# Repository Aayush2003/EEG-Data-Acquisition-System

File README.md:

# EEG Data Acquisition System

This repository contains all the work we've done as part of the course project in EE344: Electronic Design Lab

Team Members:
* Aayush Rajesh
* Anubhav Bhatla
* Aditya Sriram
* Ankith R
* Nithish Kumar Reddy
* Shivam Patel

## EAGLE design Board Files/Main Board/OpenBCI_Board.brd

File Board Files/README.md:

## PCB Design Files  

* The Base ADC Board is a modular unit which houses a single ADS1194 ADC placed on a standard 64-pin breakout board. The unit can interface with 4-channel differential electrodes and a microcontroller. In case of use in a Daisy-chain, this must be the base ADC (```DAISY_IN``` grounded) as it provides the sampling clock to all other ADCs in the chain.  
* The Daisy ADC Board is a modular unit similar to the Base ADC Board, and is meant to be connected in a Daisy-chain. Breakout pins on the board facillitate the connection according to Daisy-chain specifications.  
* The Main Board is a single, large PCB which can house 6 ADS1194 ADCs (and hence has a channel count of 24). It also has provisions for a PIC32MX microcontroller, a Wi-Fi chip, an SD card holder, and an accelerometer.

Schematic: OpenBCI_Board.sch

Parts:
C1: 10n; CAPC1608X85
C2, C4: 2.2u; CAPC1608X85
C3, C13, C23, C33, C41, C49, C56, C64, C124: 10u; CAPC3216X135
C5, C6, C8, C9, C15, C16, C19, C20, C24, C27, C29, C31, C35, C36, C38, C43, C44, C46, C51, C52, C54, C59, C60, C62, C67, C68, C70, C129, C131, C135, C137, C139, C141, C143, C145, C160, C162, C164, C166, C168, C170, C174, C176, C178, C180, C182, C184, C188, C190, C192, C194, C196, C198, C202, C204, C206, C208, C210, C212, C216, C218, C220, C222, C224, C226, C230, C232, C234, C236, C238, C240, C244, C246, C248, C250, C252, C254, C258, C260, C262, C264, C266, C268, C272, C274, C276, C278, C280, C282, C286, C288, C290, C292, C294, C296, C300: 1u; CAPC2012X110
C7, C12, C17, C21, C22, C26, C28, C30, C32, C37, C40, C45, C48, C53, C57, C61, C65, C69, C128, C130, C134, C136, C138, C140, C142, C144, C146, C147, C150, C151, C159, C161, C163, C165, C167, C169, C173, C175, C177, C179, C181, C183, C187, C189, C191, C193, C195, C197, C201, C203, C205, C207, C209, C211, C215, C217, C219, C221, C223, C225, C229, C231, C233, C235, C237, C239, C243, C245, C247, C249, C251, C253, C257, C259, C261, C263, C265, C267, C271, C273, C275, C277, C279, C281, C285, C287, C289, C291, C293, C295, C299: 0.1u; CAPC2012X110
C10, C11: 3.3u; CAPC1608X85
C14, C34, C42, C50, C58, C66: 22u; CAPC3216X135
C18: 10u; CAP_MCVV_A1_MTC-L
C25, C39, C47, C55, C63, C71: 100p; CAPC1608X85
C72, C73, C74, C76, C77, C78, C79, C80, C81, C82, C83, C84, C85, C86, C87, C88, C89, C90, C91, C92, C93, C94, C95, C96, C97, C98, C99, C100, C101, C102, C103, C104, C105, C106, C107, C108, C109, C110, C111, C112, C113, C114, C115, C116, C117, C118, C119, C121, C122, C123, C152, C153, C154, C155, C156: 10p; CAPC1608X85
C125, C126: 15p; CAPC1608X85
C127: 1.5n; CAPC1608X85
CR1, CR2: BAT85; DO-34_NEX
D1, D3: LED_BLUE; LEDC3216X75N_FLAT-B
D2: LED_BLUE; LEDC1005X25N_FLAT-B
ESP-BOOT: 10-XX; B3F-10XX
ESP-RST: 10-XX; B3F-10XX
FB1, FB2, FB3, FB5, FB6, FB9: FERRITE_BEAD; BEADC1608X95N
J3: SDCARD; GCT_MEM2051-00-195-00-A_REVD1
JP1, JP2, JP3, JP20, JP21, JP22: PINHD-2X5/90; 2X05/90
JP4, JP11, JP23: PINHD-1X2; 1X02
JP5, JP6: PINHD-2X2/90; 2X02/90
JP7: PINHD-1X10; 1X10
JP8: PINHD-1X8; 1X08
JP9, JP19: PINHD-1X4; 1X04
JP10: PINHD-1X3; 1X03
JP12: PINHD-1X7; 1X07
JP13, JP14, JP15, JP16, JP18: PINHD-1X1; 1X01
JP17: AGND; 1X01
MCLR/RESET: 10-XX; B3F-10XX
PIC-BOOT: PIC-BOOT; B3F-10XX
R1, R2, R4, R6, R7, R8, R61: 10k; RESC1608X60
R3, R5, R63, R66: 1k; RESC1608X60
R10, R11, R12, R13, R14, R15, R16, R17, R18, R19, R20, R21, R22, R23, R24, R25, R26, R27, R28, R29, R30, R31, R32, R33, R34, R35, R36, R37, R38, R39, R40, R41, R42, R43, R44, R45, R46, R47, R48, R49, R50, R51, R52, R53, R54, R55, R56, R57, R58, R59, R68, R69, R70, R71, R72: 5k; RESC1608X60
R62, R65: 1M; RESC1608X60
R64: 470k; RESC1608X60
R67: 0; RESC1608X60
U1: ESP-07SESP-07S_RFS-L; ESP-07S_RFS-L
U2: TPS72325DBVTDBV0005A; DBV0005A
U3: TLV70012QDDCRQ1DDC5_TEX-L; DDC5_TEX-L
U4, U6: AP2112K-3.3TRG1SOT_RG1_DIO-L; SOT_RG1_DIO-L
U5: LM2664M6; SOT95P280X145-6N
U7: LIS3DHHTRQFN; QFN_ICLX_STM
U8, U9, U10, U11, U12, U13: ADS1194CPAGPAG64-L; PAG64-L
U14, U15, U16, U17, U18, U19, U20, U21, U22, U23, U24, U25, U26, U27, U30: TPD4E1B; DCK6_TEX-L
U28: PIC32MX250F128D-50I/PTTQFP44_MC_MCH-L; TQFP44_MC_MCH-L
XTAL1: 8M; XTALRR488W45L1150T500H350B

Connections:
1N: JP20.7, R57.1, U25.4 (IO3)
1P: JP20.8, R58.1, U26.1 (IO1)
2N: JP20.5, R55.1, U25.2 (IO2)
2P: JP20.6, R56.1, U25.5 (IO4)
3N: JP20.3, R53.1, U24.4 (IO3)
3P: JP20.4, R54.1, U25.1 (IO1)
3V3: C19.1, C22.1, C23.1, D2.A, JP9.1, R1.2, R2.2, R4.2, U1.8 (VCC), U4.5 (VOUT)
4N: JP20.1, R51.1, U24.2 (IO2)
4P: JP20.2, R52.1, U24.5 (IO4)
5N: JP21.7, R49.1, U23.4 (IO3)
5P: JP21.8, R50.1, U24.1 (IO1)
6N: JP21.5, R47.1, U23.2 (IO2)
6P: JP21.6, R48.1, U23.5 (IO4)
7N: JP21.3, R45.1, U22.4 (IO3)
7P: JP21.4, R46.1, U23.1 (IO1)
8N: JP21.1, R43.1, U22.2 (IO2)
8P: JP21.2, R44.1, U22.5 (IO4)
9N: JP1.7, R41.1, U21.4 (IO3)
9P: JP1.8, R42.1, U22.1 (IO1)
10N: JP1.5, R39.1, U21.2 (IO2)
10P: JP1.6, R40.1, U21.5 (IO4)
11N: JP1.3, R37.1, U20.4 (IO3)
11P: JP1.4, R38.1, U21.1 (IO1)
12N: JP1.1, R35.1, U20.2 (IO2)
12P: JP1.2, R36.1, U20.5 (IO4)
13N: JP22.7, R33.1, U19.4 (IO3)
13P: JP22.8, R34.1, U20.1 (IO1)
14N: JP22.5, R31.1, U19.2 (IO2)
14P: JP22.6, R32.1, U19.5 (IO4)
15N: JP22.3, R29.1, U18.4 (IO3)
15P: JP22.4, R30.1, U19.1 (IO1)
16N: JP22.1, R27.1, U18.2 (IO2)
16P: JP22.2, R28.1, U18.5 (IO4)
17N: JP2.7, R25.1, U17.4 (IO3)
17P: JP2.8, R26.1, U18.1 (IO1)
18N: JP2.5, R23.1, U17.2 (IO2)
18P: JP2.6, R24.1, U17.5 (IO4)
19N: JP2.3, R21.1, U16.4 (IO3)
19P: JP2.4, R22.1, U17.1 (IO1)
20N: JP2.1, R19.1, U16.2 (IO2)
20P: JP2.2, R20.1, U16.5 (IO4)
21N: JP3.7, R17.1, U15.4 (IO3)
21P: JP3.8, R18.1, U16.1 (IO1)
22N: JP3.5, R15.1, U15.2 (IO2)
22P: JP3.6, R16.1, U15.5 (IO4)
23N: JP3.3, R13.1, U14.4 (IO3)
23P: JP3.4, R14.1, U15.1 (IO1)
24N: JP3.1, R11.1, U14.2 (IO2)
24P: JP3.2, R12.1, U14.5 (IO4)
-RAW: C4.1, C11.1, U2.2 (IN), U2.3 (EN), U5.2 (OUT)
AGND: C1.2, C2.2, C4.2, C5.2, C6.2, C11.2, C26.2, C27.2, C28.2, C29.2, C30.2, C31.2, C72.2, C73.2, C74.1, C74.2, C76.2, C77.2, C78.2, C79.2, C80.2, C81.2, C82.2, C83.2, C84.2, C85.2, C86.2, C87.2, C88.2, C89.2, C90.2, C91.2, C92.2, C93.2, C94.2, C95.2, C96.2, C97.2, C98.2, C99.2, C100.2, C101.2, C102.2, C103.2, C104.2, C105.2, C106.2, C107.2, C108.2, C109.2, C110.2, C111.2, C112.2, C113.2, C114.2, C115.2, C116.2, C117.2, C118.2, C119.2, C121.2, C122.2, C123.2, C128.2, C129.2, C130.2, C131.2, C134.2, C135.2, C136.2, C137.2, C138.2, C139.2, C140.2, C141.2, C142.2, C143.2, C144.2, C145.2, C152.2, C153.2, C154.2, C155.2, C156.2, C159.2, C160.2, C161.2, C162.2, C163.2, C164.2, C165.2, C166.2, C167.2, C168.2, C169.2, C170.2, C173.2, C174.2, C175.2, C176.2, C177.2, C178.2, C179.2, C180.2, C181.2, C182.2, C183.2, C184.2, C187.2, C188.2, C189.2, C190.2, C191.2, C192.2, C193.2, C194.2, C195.2, C196.2, C197.2, C198.2, C201.2, C202.2, C203.2, C204.2, C205.2, C206.2, C207.2, C208.2, C209.2, C210.2, C211.2, C212.2, C215.2, C216.2, C217.2, C218.2, C219.2, C220.2, C221.2, C222.2, C223.2, C224.2, C225.2, C226.2, C229.2, C230.2, C231.2, C232.2, C233.2, C234.2, C235.2, C236.2, C237.2, C238.2, C239.2, C240.2, C243.2, C244.2, C245.2, C246.2, C247.2, C248.2, C249.2, C250.2, C251.2, C252.2, C253.2, C254.2, C257.2, C258.2, C259.2, C260.2, C261.2, C262.2, C263.2, C264.2, C265.2, C266.2, C267.2, C268.2, C271.2, C272.2, C273.2, C274.2, C275.2, C276.2, C277.2, C278.2, C279.2, C280.2, C281.2, C282.2, C285.2, C286.2, C287.2, C288.2, C289.2, C290.2, C291.2, C292.2, C293.2, C294.2, C295.2, C296.2, C299.2, C300.2, FB1.2, FB2.2, FB3.2, FB5.2, FB6.2, FB9.2, JP4.2, JP5.3, JP5.4, JP6.3, JP6.4, JP8.2, JP11.1, JP12.7, JP13.1, JP14.1, JP15.1, JP16.1, JP17.1, JP23.2, R10.1, R10.2, U2.1 (GND), U3.2 (GND), U5.1 (GND), U8.31 (RESV1), U8.33 (DGND_2), U8.49 (DGND_3), U8.51 (DGND), U8.52 (CLKSEL), U8.60 (RLDINV_2), U9.31 (RESV1), U9.33 (DGND_2), U9.49 (DGND_3), U9.51 (DGND), U9.52 (CLKSEL), U9.60 (RLDINV_2), U10.31 (RESV1), U10.33 (DGND_2), U10.49 (DGND_3), U10.51 (DGND), U10.52 (CLKSEL), U10.60 (RLDINV_2), U11.31 (RESV1), U11.33 (DGND_2), U11.49 (DGND_3), U11.51 (DGND), U11.52 (CLKSEL), U11.60 (RLDINV_2), U12.31 (RESV1), U12.33 (DGND_2), U12.49 (DGND_3), U12.51 (DGND), U12.52 (CLKSEL), U12.60 (RLDINV_2), U13.31 (RESV1), U13.33 (DGND_2), U13.41 (DAISY_IN), U13.49 (DGND_3), U13.51 (DGND), U13.60 (RLDINV_2), U14.3 (GND), U15.3 (GND), U16.3 (GND), U17.3 (GND), U18.3 (GND), U19.3 (GND), U20.3 (GND), U21.3 (GND), U22.3 (GND), U23.3 (GND), U24.3 (GND), U25.3 (GND), U26.3 (GND), U27.1 (IO1), U27.3 (GND), U30.3 (GND)
AVDD: C5.1, C26.1, C27.1, C30.1, C31.1, C130.1, C131.1, C134.1, C135.1, C136.1, C137.1, C163.1, C164.1, C167.1, C168.1, C169.1, C170.1, C173.1, C174.1, C175.1, C176.1, C191.1, C192.1, C195.1, C196.1, C197.1, C198.1, C201.1, C202.1, C203.1, C204.1, C219.1, C220.1, C223.1, C224.1, C225.1, C226.1, C229.1, C230.1, C231.1, C232.1, C247.1, C248.1, C251.1, C252.1, C253.1, C254.1, C257.1, C258.1, C259.1, C260.1, C275.1, C276.1, C279.1, C280.1, C281.1, C282.1, C285.1, C286.1, C287.1, C288.1, JP5.1, JP5.2, U3.5 (OUT), U8.1 (IN8N), U8.2 (IN8P), U8.3 (IN7N), U8.4 (IN7P), U8.5 (IN6N), U8.6 (IN6P), U8.7 (IN5N), U8.8 (IN5P), U8.17 (TESTP_PACE_OUT1), U8.18 (TESTN_PACE_OUT2), U8.19 (AVDD_2), U8.21 (AVDD_3), U8.22 (AVDD_4), U8.42 (GPIO1), U8.44 (GPIO2), U8.45 (GPIO3), U8.46 (GPIO4), U8.54 (AVDD1), U8.56 (AVDD_5), U8.59 (AVDD), U9.1 (IN8N), U9.2 (IN8P), U9.3 (IN7N), U9.4 (IN7P), U9.5 (IN6N), U9.6 (IN6P), U9.7 (IN5N), U9.8 (IN5P), U9.17 (TESTP_PACE_OUT1), U9.18 (TESTN_PACE_OUT2), U9.19 (AVDD_2), U9.21 (AVDD_3), U9.22 (AVDD_4), U9.42 (GPIO1), U9.44 (GPIO2), U9.45 (GPIO3), U9.46 (GPIO4), U9.54 (AVDD1), U9.56 (AVDD_5), U9.59 (AVDD), U10.1 (IN8N), U10.2 (IN8P), U10.3 (IN7N), U10.4 (IN7P), U10.5 (IN6N), U10.6 (IN6P), U10.7 (IN5N), U10.8 (IN5P), U10.17 (TESTP_PACE_OUT1), U10.18 (TESTN_PACE_OUT2), U10.19 (AVDD_2), U10.21 (AVDD_3), U10.22 (AVDD_4), U10.42 (GPIO1), U10.44 (GPIO2), U10.45 (GPIO3), U10.46 (GPIO4), U10.54 (AVDD1), U10.56 (AVDD_5), U10.59 (AVDD), U11.1 (IN8N), U11.2 (IN8P), U11.3 (IN7N), U11.4 (IN7P), U11.5 (IN6N), U11.6 (IN6P), U11.7 (IN5N), U11.8 (IN5P), U11.17 (TESTP_PACE_OUT1), U11.18 (TESTN_PACE_OUT2), U11.19 (AVDD_2), U11.21 (AVDD_3), U11.22 (AVDD_4), U11.42 (GPIO1), U11.44 (GPIO2), U11.45 (GPIO3), U11.46 (GPIO4), U11.54 (AVDD1), U11.56 (AVDD_5), U11.59 (AVDD), U12.1 (IN8N), U12.2 (IN8P), U12.3 (IN7N), U12.4 (IN7P), U12.5 (IN6N), U12.6 (IN6P), U12.7 (IN5N), U12.8 (IN5P), U12.17 (TESTP_PACE_OUT1), U12.18 (TESTN_PACE_OUT2), U12.19 (AVDD_2), U12.21 (AVDD_3), U12.22 (AVDD_4), U12.42 (GPIO1), U12.44 (GPIO2), U12.45 (GPIO3), U12.46 (GPIO4), U12.54 (AVDD1), U12.56 (AVDD_5), U12.59 (AVDD), U13.1 (IN8N), U13.2 (IN8P), U13.3 (IN7N), U13.4 (IN7P), U13.5 (IN6N), U13.6 (IN6P), U13.7 (IN5N), U13.8 (IN5P), U13.17 (TESTP_PACE_OUT1), U13.18 (TESTN_PACE_OUT2), U13.19 (AVDD_2), U13.21 (AVDD_3), U13.22 (AVDD_4), U13.42 (GPIO1), U13.44 (GPIO2), U13.45 (GPIO3), U13.46 (GPIO4), U13.52 (CLKSEL), U13.54 (AVDD1), U13.56 (AVDD_5), U13.59 (AVDD), U27.2 (IO2)
AVSS: C2.1, C12.2, C13.2, C14.2, C15.2, C16.2, C17.2, C24.2, C25.2, C32.2, C33.2, C34.2, C35.2, C36.2, C37.2, C38.2, C39.2, C40.2, C41.2, C42.2, C43.2, C44.2, C45.2, C46.2, C47.2, C48.2, C49.2, C50.2, C51.2, C52.2, C53.2, C54.2, C55.2, C56.2, C57.2, C58.2, C59.2, C60.2, C61.2, C62.2, C63.2, C64.2, C65.2, C66.2, C67.2, C68.2, C69.2, C70.2, C71.2, C128.1, C129.1, C138.1, C139.1, C140.1, C141.1, C142.1, C143.1, C144.1, C145.1, C165.1, C166.1, C177.1, C178.1, C179.1, C180.1, C181.1, C182.1, C183.1, C184.1, C193.1, C194.1, C205.1, C206.1, C207.1, C208.1, C209.1, C210.1, C211.1, C212.1, C221.1, C222.1, C233.1, C234.1, C235.1, C236.1, C237.1, C238.1, C239.1, C240.1, C249.1, C250.1, C261.1, C262.1, C263.1, C264.1, C265.1, C266.1, C267.1, C268.1, C277.1, C278.1, C289.1, C290.1, C291.1, C292.1, C293.1, C294.1, C295.1, C296.1, JP6.1, JP6.2, U2.5 (OUT), U8.20 (AVSS_2), U8.23 (AVSS_3), U8.25 (VREFN), U8.32 (AVSS_4), U8.53 (AVSS1), U8.57 (AVSS_5), U8.58 (AVSS), U9.20 (AVSS_2), U9.23 (AVSS_3), U9.25 (VREFN), U9.32 (AVSS_4), U9.53 (AVSS1), U9.57 (AVSS_5), U9.58 (AVSS), U10.20 (AVSS_2), U10.23 (AVSS_3), U10.25 (VREFN), U10.32 (AVSS_4), U10.53 (AVSS1), U10.57 (AVSS_5), U10.58 (AVSS), U11.20 (AVSS_2), U11.23 (AVSS_3), U11.25 (VREFN), U11.32 (AVSS_4), U11.53 (AVSS1), U11.57 (AVSS_5), U11.58 (AVSS), U12.20 (AVSS_2), U12.23 (AVSS_3), U12.25 (VREFN), U12.32 (AVSS_4), U12.53 (AVSS1), U12.57 (AVSS_5), U12.58 (AVSS), U13.20 (AVSS_2), U13.23 (AVSS_3), U13.25 (VREFN), U13.32 (AVSS_4), U13.53 (AVSS1), U13.57 (AVSS_5), U13.58 (AVSS), U26.4 (IO3)
BATT1: CR1.2, JP4.1
BATT2: CR2.2, JP23.1
BOOT_EN: JP7.9, PIC-BOOT.1 (S), PIC-BOOT.2 (S1), R64.2, U28.2 (RPC6/PMA1/RC6)
CS_ACC: U7.4 (CS), U28.38 (RPC5/PMA3/RC5)
CS_ADC: U8.39 (!CS), U9.39 (!CS), U10.39 (!CS), U11.39 (!CS), U12.39 (!CS), U13.39 (!CS), U28.33 (SOSCI/RPB4/RB4)
CS_DAISY: JP8.8, U28.25 (AN6/RPC0/RC0)
CS_SD: J3.P2 (DATA3/CD), U28.37 (RPC4/PMA4/RC4)
DAISY_3_4: U10.41 (DAISY_IN), U11.43 (DOUT)
DGND: C3.2, C7.2, C8.2, C9.2, C18.1, C19.2, C20.2, C21.2, C22.2, C23.2, C124.1, C125.2, C126.2, C146.2, C147.2, C150.2, C151.1, ESP-BOOT.1 (S), ESP-BOOT.2 (S1), ESP-RST.3, ESP-RST.4 (P1), FB1.1, FB2.1, FB3.1, FB5.1, FB6.1, FB9.1, J3.P6 (VSS), JP7.3, JP7.10, JP9.2, JP10.3, JP18.1, MCLR/RESET.3, MCLR/RESET.4 (P1), R5.2, R6.1, R63.1, R64.1, U1.9 (GND), U4.2 (GND), U6.2 (GND), U7.9 (GND_2), U7.10 (GND_3), U7.11 (GND_4), U7.12 (GND_5), U7.13 (GND_6), U7.14 (GND_7), U7.15 (GND_8), U7.16 (GND), U28.6 (VSS_2), U28.15 (AN9/C3INA/RPB15/SCK2/CTED6/PMCS1/RB15), U28.16 (AVSS), U28.19 (PGED3/VREF+/CVREF+/AN0/C3INC/RPA0/CTED1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), U28.23 (AN4/C1INB/C2IND/RPB2/SDA2/CTED13/PMD2/R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), U28.24 (AN5/C1INA/C2INC/RTCC/RPB3/SCL2/PMWR/RB3), U28.27 (AN8/RPC2/PMA2/RC2), U28.29 (VSS_3), U28.32 (TDO/RPA8/PMA8/RA8), U28.35 (TDI/RPA9/PMA9/RA9), U28.39 (VSS), U28.44 (RPB8/SCL1/CTED10/PMD4/RB8)
DRDY: U8.47 (!DRDY), U28.43 (RPB7/CTED3/PMD5/INT0/RB7)
DVDD: C3.1, C6.1, C7.1, C8.1, C18.2, C21.1, C28.1, C29.1, C146.1, C147.1, C150.1, C159.1, C160.1, C161.1, C162.1, C187.1, C188.1, C189.1, C190.1, C215.1, C216.1, C217.1, C218.1, C243.1, C244.1, C245.1, C246.1, C271.1, C272.1, C273.1, C274.1, C299.1, C300.1, J3.P4 (VDD), JP7.2, JP8.1, PIC-BOOT.3, PIC-BOOT.4 (P1), R61.1, U3.1 (IN), U3.3 (EN), U5.4 (!SD), U5.5 (V+), U6.5 (VOUT), U7.7 (VDDIO), U7.8 (VDD), U8.35 (!PWDN), U8.48 (DVDD_2), U8.50 (DVDD), U9.35 (!PWDN), U9.48 (DVDD_2), U9.50 (DVDD), U10.35 (!PWDN), U10.48 (DVDD_2), U10.50 (DVDD), U11.35 (!PWDN), U11.48 (DVDD_2), U11.50 (DVDD), U12.35 (!PWDN), U12.48 (DVDD_2), U12.50 (DVDD), U13.35 (!PWDN), U13.48 (DVDD_2), U13.50 (DVDD), U28.10 (VUSB3V3), U28.17 (AVDD), U28.28 (VDD_2), U28.40 (VDD), U28.42 (VBUS)
ESP_SS: R6.2, U1.10 (IO15), U28.1 (RPB9/SDA1/CTED4/PMD3/RB9)
GPIO1: JP19.1, U28.4 (RPC8/PMA5/RC8)
GPIO2: JP19.2, U28.5 (RPC9/CTED7/PMA6/RC9)
GPIO3: JP19.3, U28.8 (PGED2/RPB10/D+/CTED11/RB10)
GPIO4: JP19.4, U28.9 (PGEC2/RPB11/D-/RB11)
IN1N: C123.1, R57.2, U8.15 (IN1N)
IN1P: C122.1, R58.2, U8.16 (IN1P)
IN2N: C117.1, R55.2, U8.13 (IN2N)
IN2P: C116.1, R56.2, U8.14 (IN2P)
IN3N: C119.1, R53.2, U8.11 (IN3N)
IN3P: C118.1, R54.2, U8.12 (IN3P)
IN4N: C113.1, R51.2, U8.9 (IN4N)
IN4P: C112.1, R52.2, U8.10 (IN4P)
IN5N: C115.1, R49.2, U9.15 (IN1N)
IN5P: C114.1, R50.2, U9.16 (IN1P)
IN6N: C109.1, R47.2, U9.13 (IN2N)
IN6P: C108.1, R48.2, U9.14 (IN2P)
IN7N: C111.1, R45.2, U9.11 (IN3N)
IN7P: C110.1, R46.2, U9.12 (IN3P)
IN8N: C105.1, R43.2, U9.9 (IN4N)
IN8P: C104.1, R44.2, U9.10 (IN4P)
IN9N: C107.1, R41.2, U10.15 (IN1N)
IN9P: C106.1, R42.2, U10.16 (IN1P)
IN10N: C101.1, R39.2, U10.13 (IN2N)
IN10P: C100.1, R40.2, U10.14 (IN2P)
IN11N: C103.1, R37.2, U10.11 (IN3N)
IN11P: C102.1, R38.2, U10.12 (IN3P)
IN12N: C97.1, R35.2, U10.9 (IN4N)
IN12P: C96.1, R36.2, U10.10 (IN4P)
IN13N: C99.1, R33.2, U11.15 (IN1N)
IN13P: C98.1, R34.2, U11.16 (IN1P)
IN14N: C93.1, R31.2, U11.13 (IN2N)
IN14P: C92.1, R32.2, U11.14 (IN2P)
IN15N: C95.1, R29.2, U11.11 (IN3N)
IN15P: C94.1, R30.2, U11.12 (IN3P)
IN16N: C89.1, R27.2, U11.9 (IN4N)
IN16P: C88.1, R28.2, U11.10 (IN4P)
IN17N: C91.1, R25.2, U12.15 (IN1N)
IN17P: C90.1, R26.2, U12.16 (IN1P)
IN18N: C85.1, R23.2, U12.13 (IN2N)
IN18P: C84.1, R24.2, U12.14 (IN2P)
IN19N: C87.1, R21.2, U12.11 (IN3N)
IN19P: C86.1, R22.2, U12.12 (IN3P)
IN20N: C81.1, R19.2, U12.9 (IN4N)
IN20P: C80.1, R20.2, U12.10 (IN4P)
IN21N: C83.1, R17.2, U13.15 (IN1N)
IN21P: C82.1, R18.2, U13.16 (IN1P)
IN22N: C77.1, R15.2, U13.13 (IN2N)
IN22P: C76.1, R16.2, U13.14 (IN2P)
IN23N: C79.1, R13.2, U13.11 (IN3N)
IN23P: C78.1, R14.2, U13.12 (IN3P)
IN24N: C73.1, R11.2, U13.9 (IN4N)
IN24P: C72.1, R12.2, U13.10 (IN4P)
INT1: U7.6 (INT1), U28.21 (PGED1/AN2/C1IND/C2INB/C3IND/RPB0/PMD0/R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)
MCLK: JP8.6, U8.37 (CLK), U9.37 (CLK), U10.37 (CLK), U11.37 (CLK), U12.37 (CLK), U13.37 (CLK)
MCLR: JP7.1, R66.1, U28.18 (!MCLR)
MISO_1: JP8.3, JP12.1, U8.43 (DOUT), U28.41 (RPB5/USBID/RB5)
MISO_2: J3.P7 (DATA0), JP12.3, U1.6 (IO12), U7.3 (SDO), U28.34 (SOSCO/RPA4/T1CK/CTED9/RA4)
MOSI_1: JP8.7, JP12.2, U8.34 (DIN), U9.34 (DIN), U10.34 (DIN), U11.34 (DIN), U12.34 (DIN), U13.34 (DIN), U28.20 (PGEC3/VREF-/CVREF-/AN1/RPA1/CTED2/PMD6/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)
MOSI_2: J3.P3 (CMD), JP12.4, U1.7 (IO13), U7.2 (SDI), U28.22 (PGEC1/AN3/C1INC/C2INA/RPB1/CTED12/PMD1/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)
unnamed: R2.1, U1.3 (EN)
unnamed: ESP-RST.1 (S), ESP-RST.2 (S1), R1.1, U1.1 (RST)
unnamed: D1.A, U1.14 (IO5)
unnamed: D1.C, R5.1
unnamed: ESP-BOOT.3, ESP-BOOT.4 (P1), R3.1, U1.12 (IO0)
unnamed: D2.C, R3.2
unnamed: R4.1, U1.11 (IO2)
unnamed: C1.1, U2.4 (FB)
unnamed: R7.2, U4.3 (EN)
unnamed: C20.1, CR2.1, R7.1, U4.1 (VIN)
unnamed: C10.1, U5.6 (CAP+)
unnamed: C10.2, U5.3 (CAP-)
unnamed: R8.2, U6.3 (EN)
unnamed: D3.A, R67.1
unnamed: C151.2, MCLR/RESET.1 (S), MCLR/RESET.2 (S1), R61.2, R66.2
unnamed: C12.1, C13.1, U8.24 (VREFP)
unnamed: C14.1, U8.28 (VCAP1)
unnamed: C15.1, U8.30 (VCAP2)
unnamed: C16.1, U8.26 (VCAP4)
unnamed: C17.1, C24.1, U8.55 (VCAP3)
unnamed: C25.1, U8.64 (WCT)
unnamed: C32.1, C33.1, U9.24 (VREFP)
unnamed: C34.1, U9.28 (VCAP1)
unnamed: C35.1, U9.30 (VCAP2)
unnamed: C36.1, U9.26 (VCAP4)
unnamed: C37.1, C38.1, U9.55 (VCAP3)
unnamed: C39.1, U9.64 (WCT)
unnamed: C40.1, C41.1, U10.24 (VREFP)
unnamed: C42.1, U10.28 (VCAP1)
unnamed: C43.1, U10.30 (VCAP2)
unnamed: C44.1, U10.26 (VCAP4)
unnamed: C45.1, C46.1, U10.55 (VCAP3)
unnamed: C47.1, U10.64 (WCT)
unnamed: C48.1, C49.1, U11.24 (VREFP)
unnamed: C50.1, U11.28 (VCAP1)
unnamed: C51.1, U11.30 (VCAP2)
unnamed: C52.1, U11.26 (VCAP4)
unnamed: C53.1, C54.1, U11.55 (VCAP3)
unnamed: C55.1, U11.64 (WCT)
unnamed: C124.2, U28.7 (VCAP)
unnamed: C125.1, R65.2, U28.31 (OSC2/CLKO/RPA3/RA3), XTAL1.2
unnamed: C126.1, R65.1, U28.30 (OSC1/CLKI/RPA2/RA2), XTAL1.1
unnamed: C127.1, R62.2, U13.63 (RLDOUT)
unnamed: C56.1, C57.1, U12.24 (VREFP)
unnamed: C58.1, U12.28 (VCAP1)
unnamed: C59.1, U12.30 (VCAP2)
unnamed: C60.1, U12.26 (VCAP4)
unnamed: C61.1, C62.1, U12.55 (VCAP3)
unnamed: C63.1, U12.64 (WCT)
unnamed: D3.C, R63.2
unnamed: C64.1, C65.1, U13.24 (VREFP)
unnamed: C66.1, U13.28 (VCAP1)
unnamed: C67.1, U13.30 (VCAP2)
unnamed: C68.1, U13.26 (VCAP4)
unnamed: C69.1, C70.1, U13.55 (VCAP3)
unnamed: C71.1, U13.64 (WCT)
unnamed: U12.41 (DAISY_IN), U13.43 (DOUT)
unnamed: U11.41 (DAISY_IN), U12.43 (DOUT)
unnamed: U9.41 (DAISY_IN), U10.43 (DOUT)
unnamed: U8.41 (DAISY_IN), U9.43 (DOUT)
PGC: JP7.5, U28.13 (PGEC/TCK/CTED8/PMA7/RA7)
PGD: JP7.4, R67.2, U28.12 (PGED/TMS/PMA10/RA10)
RAW: C9.1, CR1.1, R8.1, U6.1 (VIN)
RESET: JP8.5, JP12.6, U8.36 (!RESET), U9.36 (!RESET), U10.36 (!RESET), U11.36 (!RESET), U12.36 (!RESET), U13.36 (!RESET), U28.26 (AN7/RPC1/RC1)
RLD1: JP20.10, R59.1, U26.2 (IO2)
RLD2: JP21.10, R71.1, U30.5 (IO4)
RLD3: JP1.10, R70.1, U30.2 (IO2)
RLD4: JP22.10, R69.1, U30.1 (IO1)
RLD5: JP2.10, R68.1, U27.4 (IO3)
RLD6: JP3.10, R72.1, U27.5 (IO4)
RLDIN1: C121.1, R59.2, U8.62 (RLDIN)
RLDIN2: C152.1, R71.2, U9.62 (RLDIN)
RLDIN3: C153.1, R70.2, U10.62 (RLDIN)
RLDIN4: C154.1, R69.2, U11.62 (RLDIN)
RLDIN5: C155.1, R68.2, U12.62 (RLDIN)
RLDIN6: C156.1, R72.2, U13.62 (RLDIN)
RLDINV: C127.2, JP11.2, R62.1, U8.61 (RLDINV), U9.61 (RLDINV), U10.61 (RLDINV), U11.61 (RLDINV), U12.61 (RLDINV), U13.61 (RLDINV)
RXD: JP9.3, U1.15 (RXD0)
SCLK: J3.P5 (CLK), JP8.4, JP12.5, U1.5 (IO14), U7.1 (SPC), U8.40 (SCLK), U9.40 (SCLK), U10.40 (SCLK), U11.40 (SCLK), U12.40 (SCLK), U13.40 (SCLK), U28.14 (CVREFOUT/AN10/C3INB/RPB14/VBUSON/SCK1/C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)
SRB1: JP20.9
SRB2: JP21.9
SRB3: JP1.9
SRB4: JP22.9
SRB5: JP2.9
SRB6: JP3.9
START: U8.38 (START), U9.38 (START), U10.38 (START), U11.38 (START), U12.38 (START), U13.38 (START), U28.36 (AN12/RPC3/RC3)
TXD: JP9.4, U1.16 (TXDO)
U1RX: JP10.1, U28.11 (AN11/RPB13/CTPLS/PMRD/RB13)
U1TX: JP10.2, U28.3 (RPC7/PMA0/RC7)

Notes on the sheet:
Daisy-Chain ADCs (Part 1)
ESD Protection
ADS 1194
Daisy-Chain ADCs (Part 2)
Wi-Fi Module
Power Components
Battery Connectors
Voltage Inverter
+2.5V Regulator
-2.5V Regulator
3.3V Regulator
3.3V Regulator (Wi-Fi)
Peripherals
Accelerometer
SD Card
PIC32 Microcontroller
Pin Headers
PICkit4
Daisy
Electrode Inputs
Wi-Fi Programming Pins
Ferrite Beads
UART
SPI Test
GND Test
uC GPIO

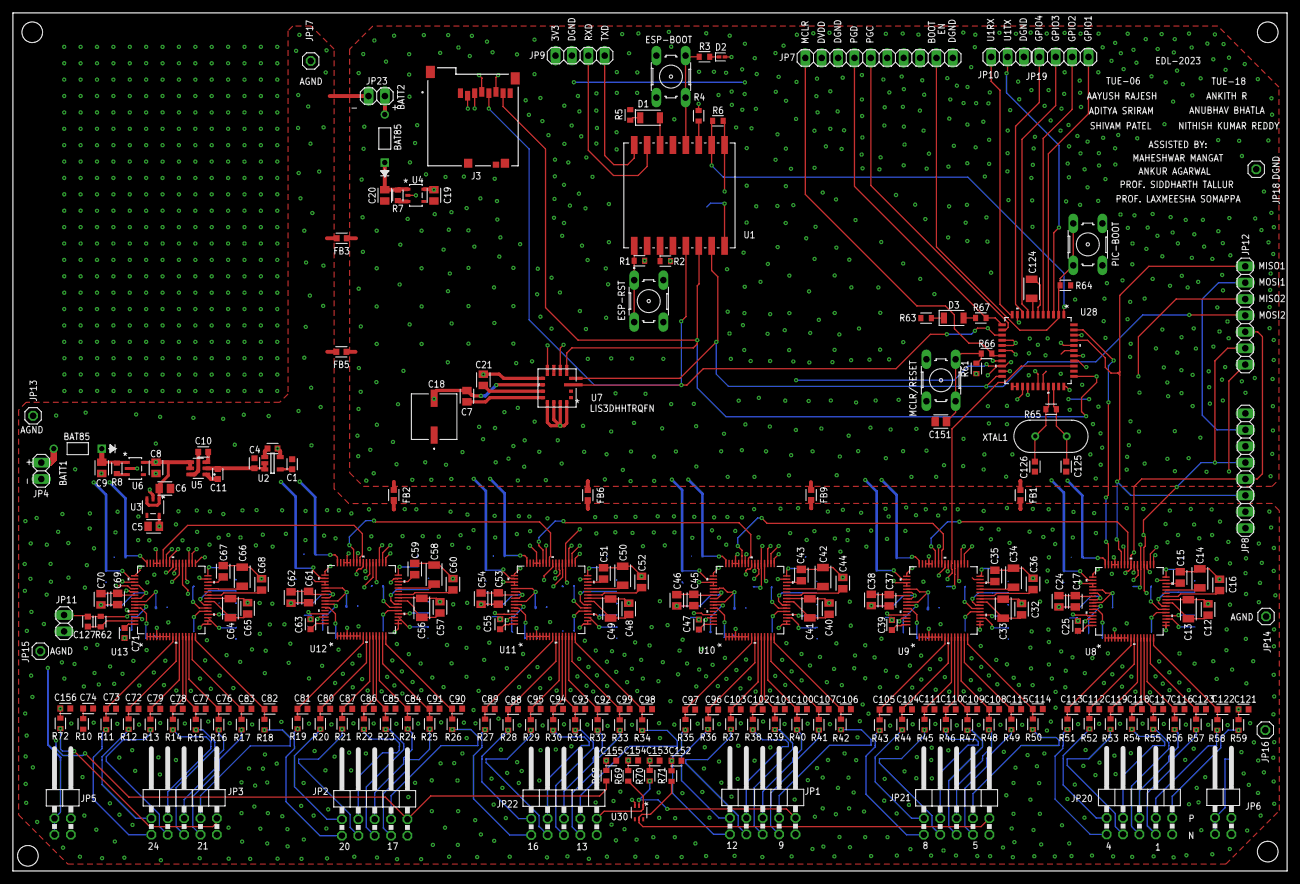
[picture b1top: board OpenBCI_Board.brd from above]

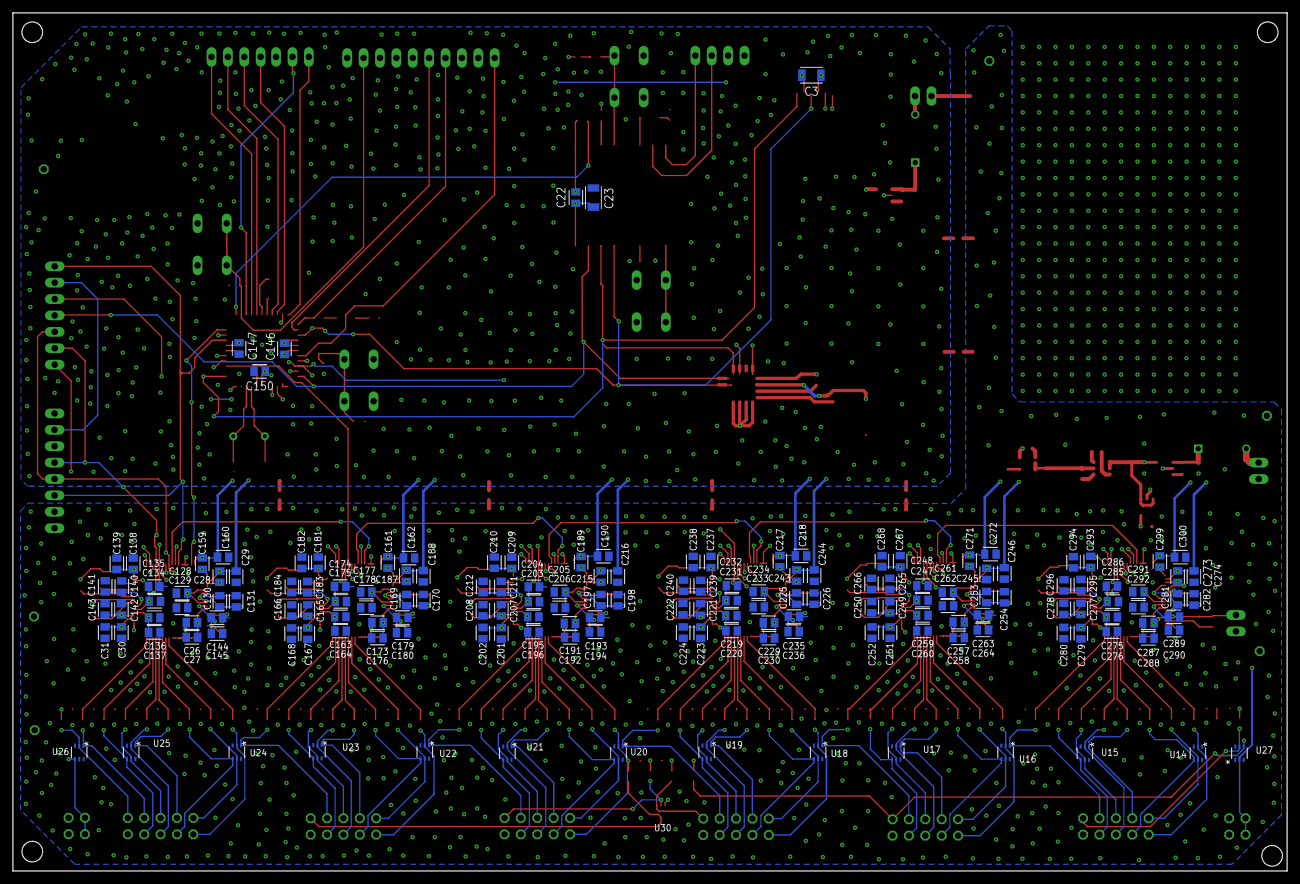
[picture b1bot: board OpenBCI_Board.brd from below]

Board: 4 copper layers, 197.5 x 133.0 mm, 411 parts (164 on the bottom side), 207 nets.

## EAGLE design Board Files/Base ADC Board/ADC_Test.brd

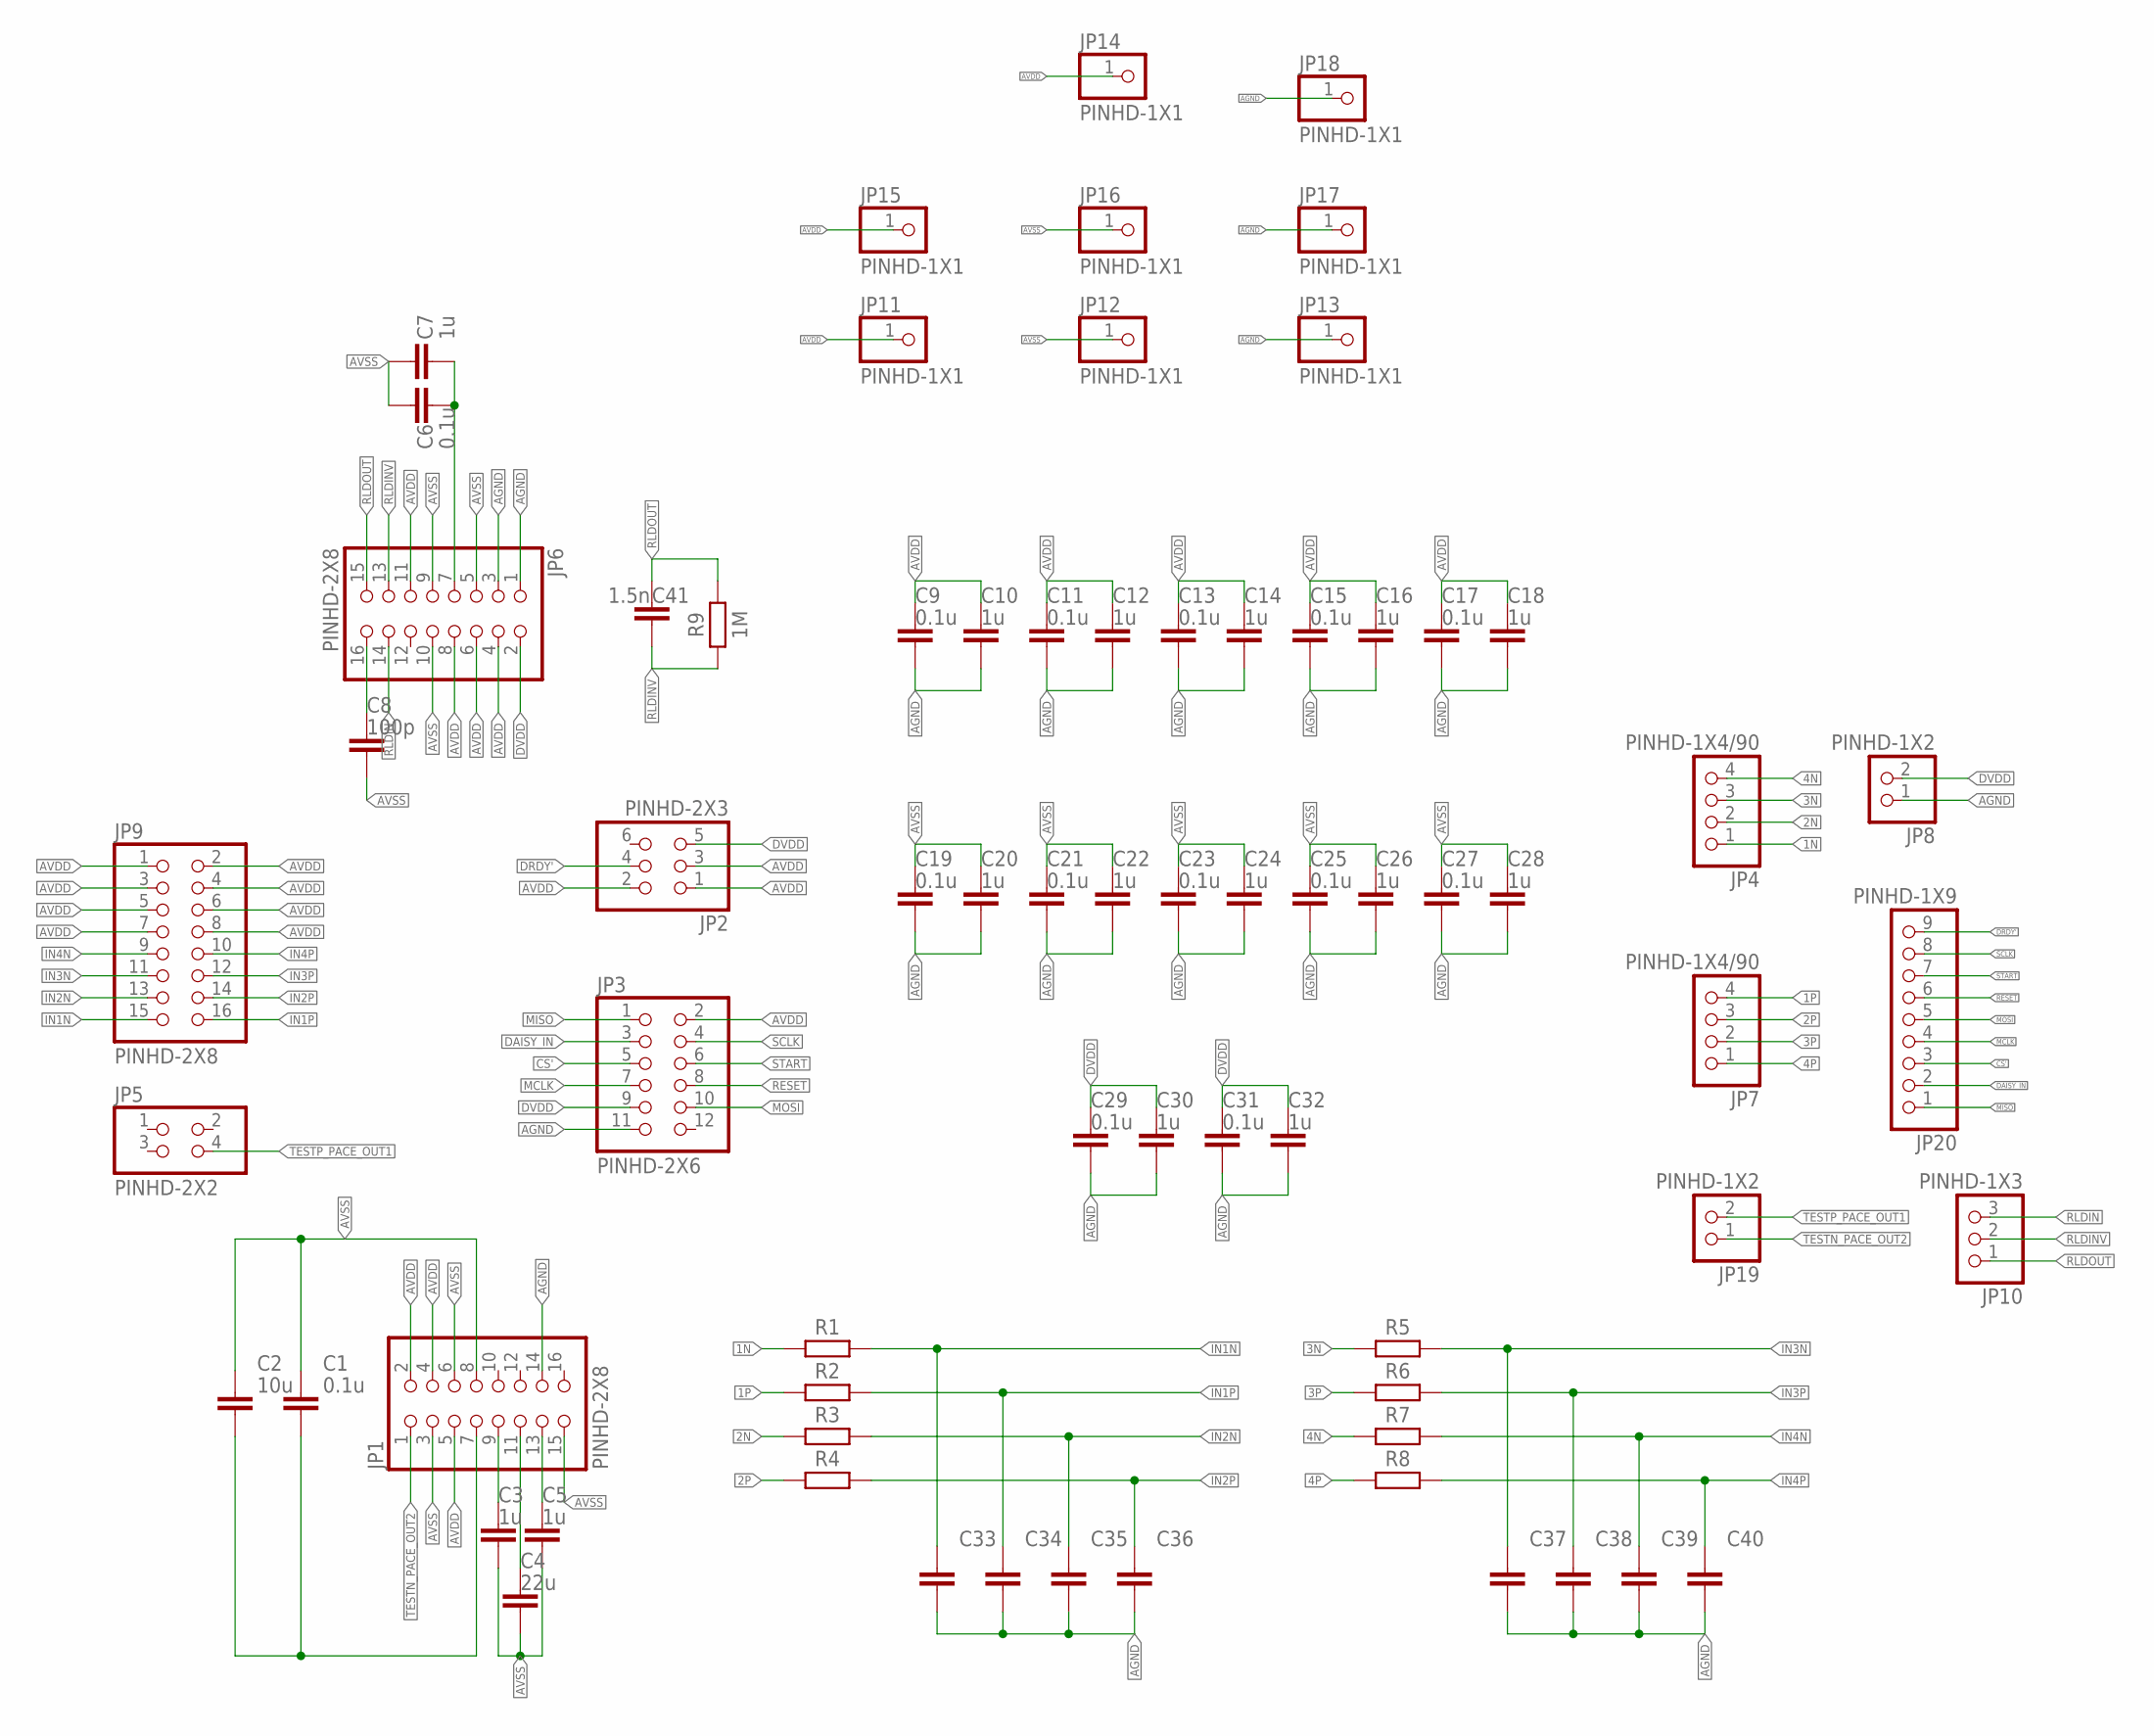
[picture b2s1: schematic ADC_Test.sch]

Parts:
C1, C6, C9, C11, C13, C15, C17, C19, C21, C23, C25, C27, C29, C31: 0.1u; CAPC2012X110
C2: 10u; CAPC2012X110
C3, C5, C7, C10, C12, C14, C16, C18, C20, C22, C24, C26, C28, C30, C32: 1u; CAPC2012X110
C4: 22u; CAPC2012X110
C8: 100p; CAPC2012X110
C33, C34, C35, C36, C37, C38, C39, C40: C_CHIP-0805(2012-METRIC); CAPC2012X110
C41: 1.5n; CAPC2012X110
JP1, JP6, JP9: PINHD-2X8; 2X08
JP2: PINHD-2X3; 2X03
JP3: PINHD-2X6; 2X06
JP4, JP7: PINHD-1X4/90; 1X04/90
JP5: PINHD-2X2; 2X02
JP8, JP19: PINHD-1X2; 1X02
JP10: PINHD-1X3; 1X03
JP11, JP12, JP13, JP14, JP15, JP16, JP17, JP18: PINHD-1X1; 1X01
JP20: PINHD-1X9; 1X09
R1, R2, R3, R4, R5, R6, R7, R8: R_CHIP-1206(3216-METRIC); RESC3216X70
R9: 1M; RESC3216X70

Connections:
1N: JP4.1, R1.1
1P: JP7.4, R2.1
2N: JP4.2, R3.1
2P: JP7.3, R4.1
3N: JP4.3, R5.1
3P: JP7.2, R6.1
4N: JP4.4, R7.1
4P: JP7.1, R8.1
AGND: C9.2, C10.2, C11.2, C12.2, C13.2, C14.2, C15.2, C16.2, C17.2, C18.2, C19.2, C20.2, C21.2, C22.2, C23.2, C24.2, C25.2, C26.2, C27.2, C28.2, C29.2, C30.2, C31.2, C32.2, C33.2, C34.2, C35.2, C36.2, C37.2, C38.2, C39.2, C40.2, JP1.14, JP3.11, JP6.1, JP6.3, JP8.1, JP13.1, JP17.1, JP18.1
AVDD: C9.1, C10.1, C11.1, C12.1, C13.1, C14.1, C15.1, C16.1, C17.1, C18.1, JP1.2, JP1.4, JP1.5, JP2.1, JP2.2, JP2.3, JP3.2, JP6.4, JP6.6, JP6.8, JP6.11, JP9.1, JP9.2, JP9.3, JP9.4, JP9.5, JP9.6, JP9.7, JP9.8, JP11.1, JP14.1, JP15.1
AVSS: C1.1, C2.1, C3.2, C4.2, C5.2, C6.1, C7.1, C8.2, C19.1, C20.1, C21.1, C22.1, C23.1, C24.1, C25.1, C26.1, C27.1, C28.1, JP1.3, JP1.6, JP1.8, JP1.15, JP6.5, JP6.9, JP6.10, JP12.1, JP16.1
CS': JP3.5, JP20.3
DAISY_IN: JP3.3, JP20.2
DRDY': JP2.4, JP20.9
DVDD: C29.1, C30.1, C31.1, C32.1, JP2.5, JP3.9, JP6.2, JP8.2
IN1N: C33.1, JP9.15, R1.2
IN1P: C34.1, JP9.16, R2.2
IN2N: C35.1, JP9.13, R3.2
IN2P: C36.1, JP9.14, R4.2
IN3N: C37.1, JP9.11, R5.2
IN3P: C38.1, JP9.12, R6.2
IN4N: C39.1, JP9.9, R7.2
IN4P: C40.1, JP9.10, R8.2
MCLK: JP3.7, JP20.4
MISO: JP3.1, JP20.1
MOSI: JP3.10, JP20.5
unnamed: C3.1, JP1.9
unnamed: C4.1, JP1.11
unnamed: C5.1, JP1.13
unnamed: C6.2, C7.2, JP6.7
unnamed: C8.1, JP6.16
unnamed: C1.2, C2.2, JP1.7
RESET: JP3.8, JP20.6
RLDIN: JP6.14, JP10.3
RLDINV: C41.2, JP6.13, JP10.2, R9.1
RLDOUT: C41.1, JP6.15, JP10.1, R9.2
SCLK: JP3.4, JP20.8
START: JP3.6, JP20.7
TESTN_PACE_OUT2: JP1.1, JP19.1
TESTP_PACE_OUT1: JP5.4, JP19.2

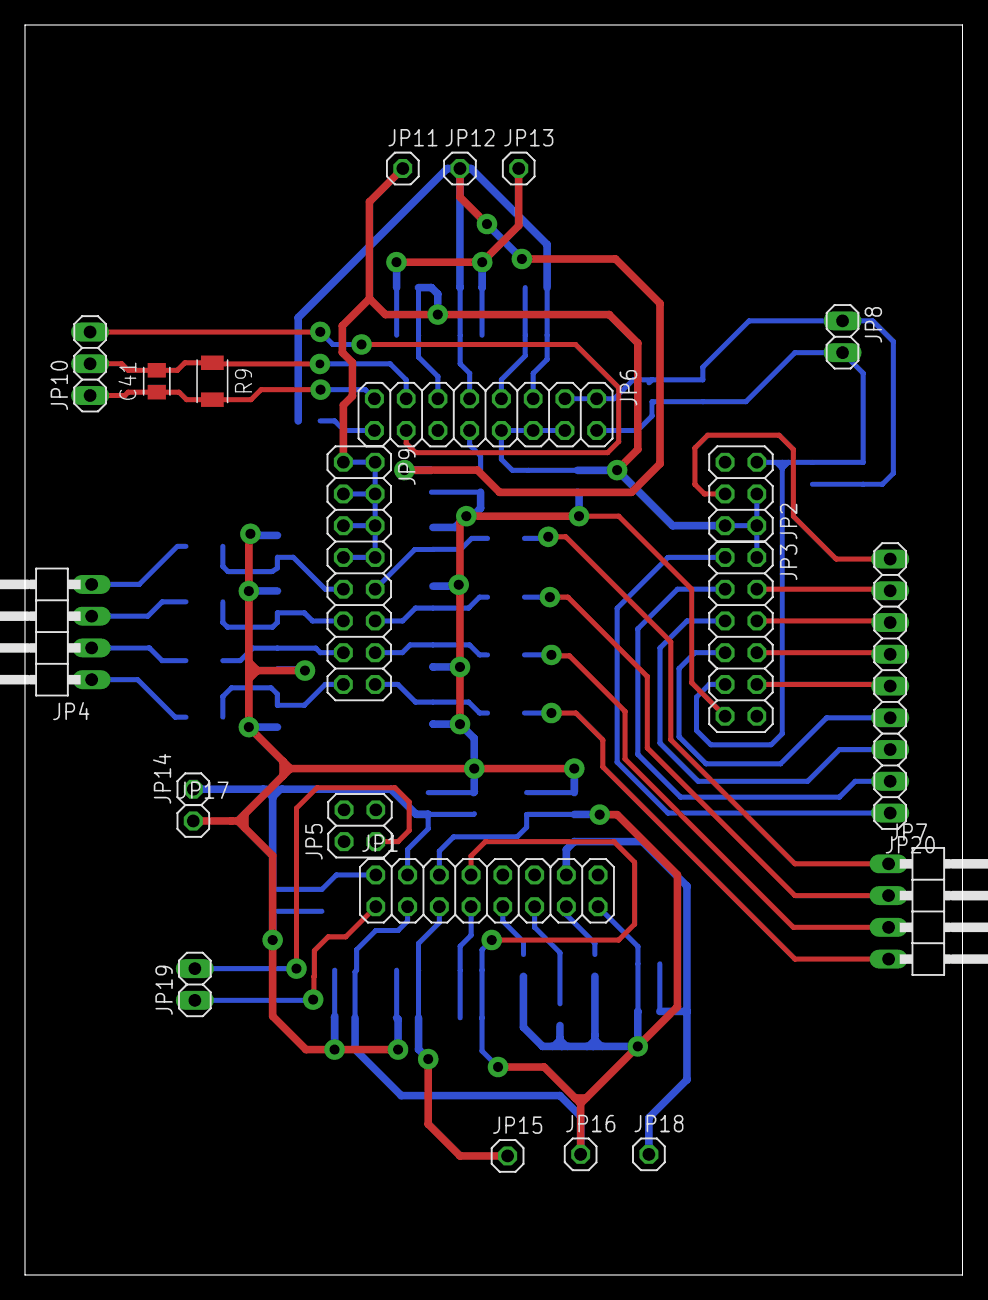
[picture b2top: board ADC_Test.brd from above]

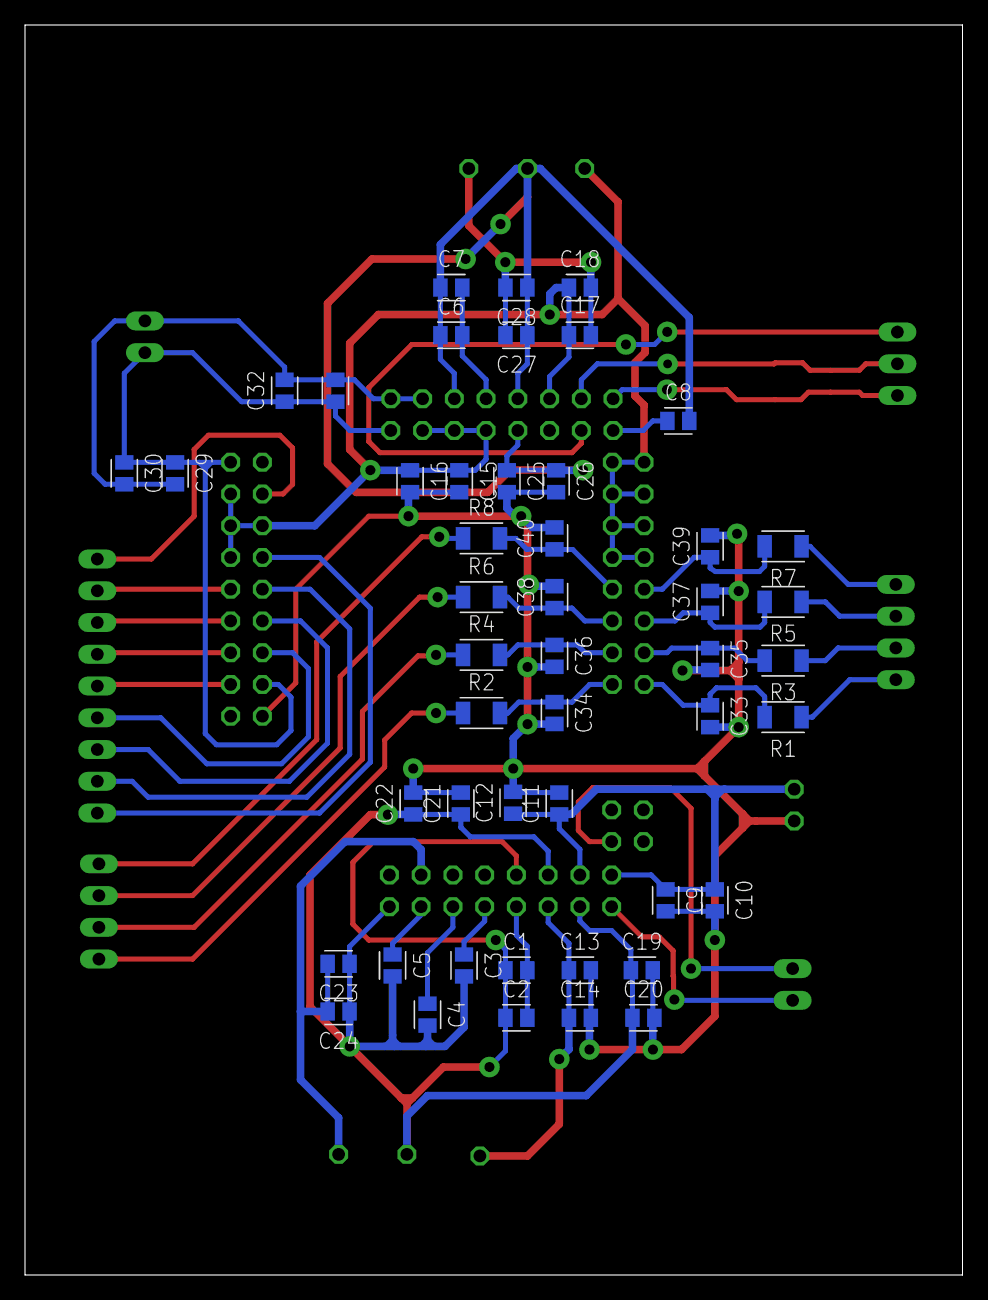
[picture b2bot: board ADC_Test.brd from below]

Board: 2 copper layers, 75.0 x 100.0 mm, 70 parts (48 on the bottom side), 40 nets.

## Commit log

2023-04-30 Added all files
2023-06-01 Create README.md for PCB Design

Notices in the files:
parts and their libraries:
COPYRIGHT: Copyright (C) 2023 Ultra Librarian. All rights reserved.
